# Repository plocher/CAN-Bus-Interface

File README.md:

# Protoboard-CANBus
## License: CERN Open Hardware Licence v1.2

The CANBus Breadboard interface is a simple experimenter's interface
to the new, experimental CAN bus based NMRANet model railroad control
bus. It is similar to, and derived from the LEDuino, which (at this
writing) is no longer available.

## CANBus Breadboard Interface features

  * 5v power input taken from breadboard
  * A complete hardware interface to the industry standard CAN Bus
  * A single EuroStyle 4 pin commector (5v, H, L, Gnd)
  * Optional LED "RX", "TX", and "Interrupt" feedback
  * All MCP2551 communication pins available for connection to appropriate processor input and output pins.

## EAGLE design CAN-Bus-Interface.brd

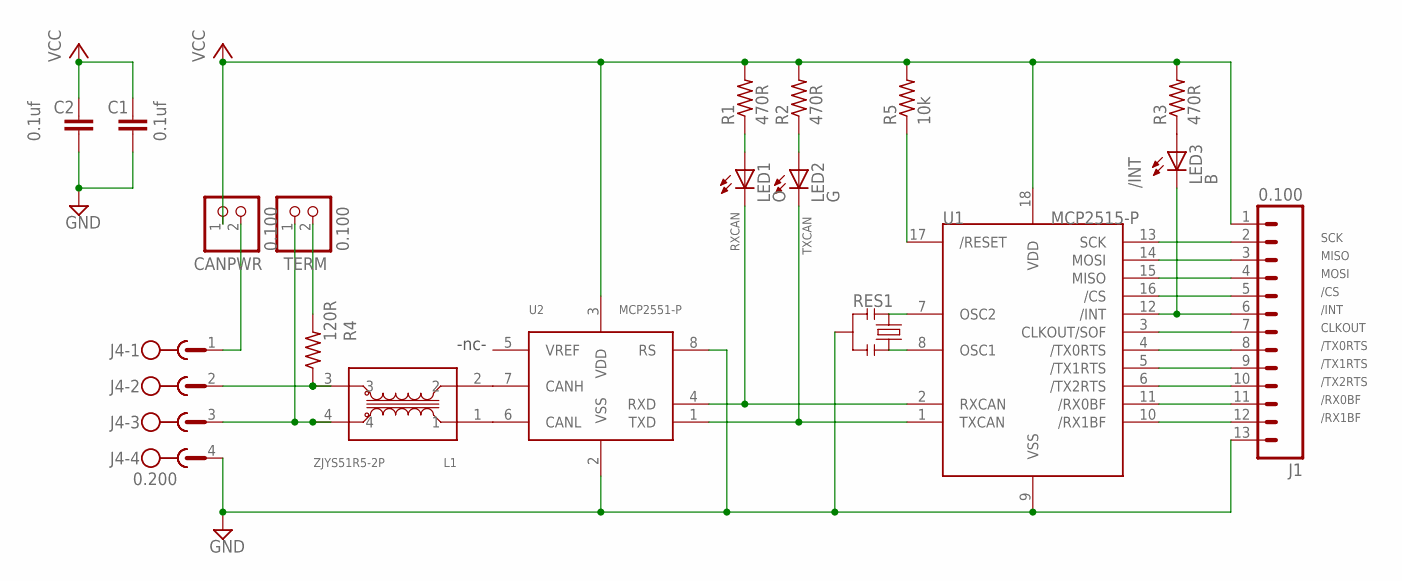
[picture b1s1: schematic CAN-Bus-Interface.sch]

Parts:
C1, C2: 0.1uf; CAP-PTH-SMALL2
CANPWR: 0.100; 1X02
J1: 0.100; 1X13
J4: 0.200; MSTBV4
L1: ZJYS51R5-2P; ZJYS
LED1: O; Q62902-B155
LED2: G; Q62902-B155
LED3: B; Q62902-B155
R1, R2, R3: 470R; 0204/5
R4: 120R; 0204/5
R5: 10k; 0204/5
RES1: RESONATORPTH; RESONATOR-PTH
TERM: 0.100; 1X02
U1: MCP2515-P; DIL18
U2: MCP2551-P; DIL08

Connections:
/CS: J1.5, U1.16 (/CS)
/INT: J1.6, LED3.A (C), U1.12 (/INT)
/RESET: R5.1, U1.17 (/RESET)
/RX0BF: J1.11, U1.11 (/RX0BF)
/RX1BF: J1.12, U1.10 (/RX1BF)
/TX0RTS: J1.8, U1.4 (/TX0RTS)
/TX1RTS: J1.9, U1.5 (/TX1RTS)
/TX2RTS: J1.10, U1.6 (/TX2RTS)
CLKOUT: J1.7, U1.3 (CLKOUT/SOF)
GND: C1.2, C2.2, J1.13, J4.4, RES1.2, U1.9 (VSS), U2.2 (VSS), U2.8 (RS)
MISO: J1.3, U1.14 (MOSI)
MOSI: J1.4, U1.15 (MISO)
unnamed: CANPWR.2, J4.1
unnamed: L1.1, U2.6 (CANL)
unnamed: L1.2, U2.7 (CANH)
unnamed: J4.2, L1.3, R4.1
unnamed: J4.3, L1.4, TERM.1
unnamed: R4.2, TERM.2
unnamed: LED1.K (A), R1.1
unnamed: LED2.K (A), R2.1
unnamed: LED3.K (A), R3.1
OSC1: RES1.3, U1.8 (OSC1)
OSC2: RES1.1, U1.7 (OSC2)
RXCAN: LED1.A (C), U1.2 (RXCAN), U2.4 (RXD)
SCK: J1.2, U1.13 (SCK)
TXCAN: LED2.A (C), U1.1 (TXCAN), U2.1 (TXD)
VCC: C1.1, C2.1, CANPWR.1, J1.1, R1.2, R2.2, R3.2, R5.2, U1.18 (VDD), U2.3 (VDD)

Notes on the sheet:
-nc-

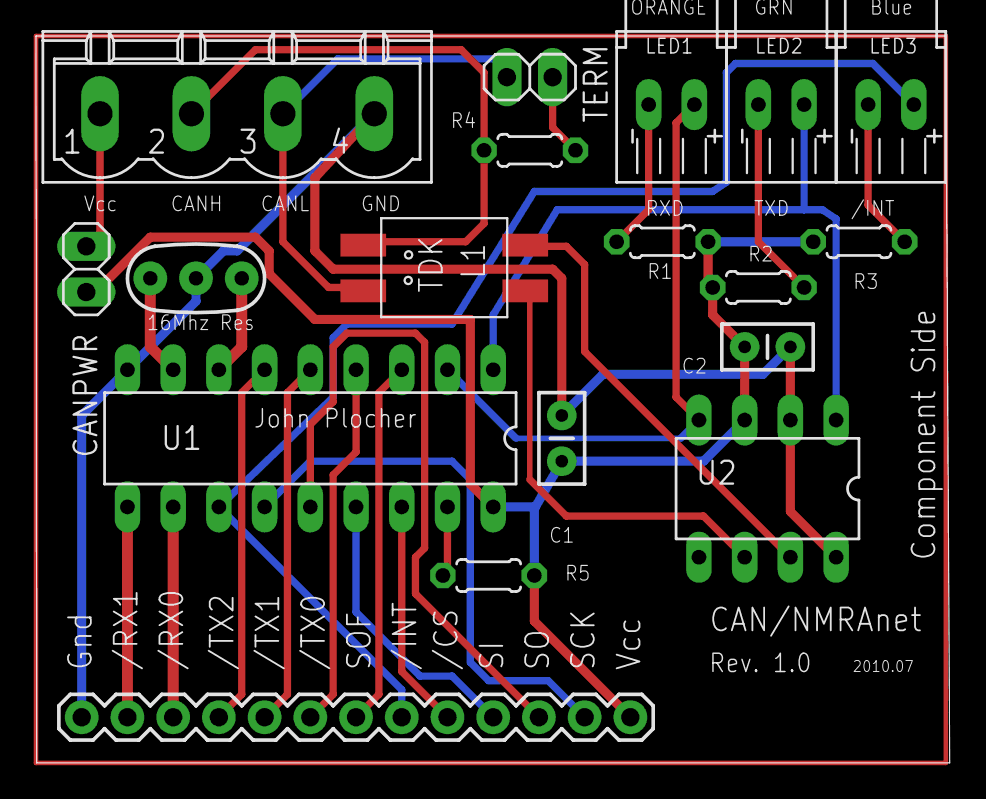
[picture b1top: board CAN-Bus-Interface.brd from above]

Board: 2 copper layers, 50.8 x 40.4 mm, 18 parts (0 on the bottom side), 27 nets.

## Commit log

2019-12-09 added graphic
2020-05-04 updated tags
2020-10-05 added values for connectors
2020-10-06 normalized values
